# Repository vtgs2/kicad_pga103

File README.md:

# kicad_pga103

KiCAD Designs for PGA-103+ Preamplifier (LNA) intended for use in VHF / UHF Satellite Reception.  

This is a catchall repo for multiple designs and multiple variants.  
The variants will be based on physical size, enclosure dimensions, and specific features.  
This is a fluid repo that wil be changing as time allows to include updates for parts selection and user guide for how to configure for different bands.  

## Shut up and give me the board

Completed Designs:
- v2.0.0.0, rev-, Oct 2, 2023
- v2.1.X.0, rev-, Oct 2, 2023
- v2.2.X.0, rev-, Oct 2, 2023

#### Osh Park:
[v2.0.0.0, rev-](https://oshpark.com/shared_projects/KYiMNU72)  
[v2.1.X.0, rev-](https://oshpark.com/shared_projects/wypFvs1c)  
[v2.2.X.0, rev-](https://oshpark.com/shared_projects/yOYgdtt8)  

## Major Design Features

### Active Device
Primary active device is the popular [PGA-103+](https://www.minicircuits.com/WebStore/dashboard.html?model=PGA-103%2B).
Expect >20 dB Gain and <1.0 dB Noise Figure for both VHF and UHF bands.  

### Bias Options
Multiple biasing options via solder jumpers on the board.  
See board silkscreen for solder jumper settings for selecting the methods described below.

#### DC on Coax, +12V
The primary expected method for powering the board.  
This method routes DC power from the output RF connector to the internal voltage regulator for power conditioning, filtering, and biasing the amp.  
A bias-t will be required on the other end of the coax close to the radio.  
A custom Bias-T design may be added to this repo, but for now here are some COTS options:
- Minicircuits [ZDPLX-2150-S+](https://www.minicircuits.com/WebStore/dashboard.html?model=ZDPLX-2150-S%2B) where the Low Pass port is for DC. Be careful about current draw requirements if using long coax runs as this has a fairly low current limit of about 100mA.  Have succesfully used this on multiple compact systems in the past.
- Minicircuits [ZABT-2R15G+](https://www.minicircuits.com/WebStore/dashboard.html?model=ZABT-2R15G%2B). This Bias-T allows 3A of DC current and also includes ability to inject a 10 MHz reference signal (not needed for this specific preamp design, but might be useful for future projects for distributing REF oscillator signals to antenna mounted components such as downconverters).
- [Kuhne Electronic Bias-Ts](https://www.kuhne-electronic.com/funk/en/shop/industrial/prof-passive-compone/prof-bias-tees/).  Pricey, but work well. They offer N and SMA variants.

##### Lightning Arrestors
If using the DC on coax methods and if using lightning arrestors (you should be!), be sure to select arrestors that allow DC pass through.  I typically connect bias-ts directly to the lightning arrestors inside the enclosure on the 'equipment' side of the arrestor using barrel N or SMA connectors.

#### DC on Coax, Direct 5V
DC on coax can be routed to AVOID the onboard voltage regulator and directly bias the PGA-103+ device.  
This method may be suitable for SDRs that have built in Bias-Ts, such as the popular [RTL-SDR](https://www.rtl-sdr.com/buy-rtl-sdr-dvb-t-dongles/) that has a built in 4.5V bias-T.

#### External DC
This method does not interact with RF output connector and supplies power to the onboard voltage regulator.  
The supplied DC Voltage should be between 6V and 16V as measured at the board input pads (consider DC voltage drop if running long external power lines).  
The current mechanical designs for enclosure do not include penetrations for external power.  
If adding external power, feed through capacitors / EMI filters are recommended. Something like [this](https://www.digikey.com/en/products/detail/tusonix-a-subsidiary-of-cts-electronic-components/4400-034LF/2079728).

## Version Description
Versioning is inspired by MAJOR.MINOR.PATCH type versioning....but will also be breaking the rules for that on purpose.

Version Fields:  ENCLOSURE.FILTER.BAND.GAIN
##### ENCLOSURE:  
1.X.X.X  [1550Z101](https://www.digikey.com/en/products/detail/hammond-manufacturing/1550Z101/2268541)  
2.X.X.X  [AN-1301-A](https://www.digikey.com/en/products/detail/bud-industries/AN-1301-A/5804533)

Enclosure style essentially dictates the board outline.

##### FILTER Style:  
X.0.X.X  No Filter  
X.1.X.X  [RBP-XXX Filter](https://www.minicircuits.com/WebStore/dashboard.html?model=RBP-140%2B)  
X.2.X.X  [SBXP-XXX Filter](https://www.minicircuits.com/WebStore/dashboard.html?model=SXBP-140%2B)

##### BAND:   
X.X.0.X  Wideband  
X.X.1.X  VHF  
X.X.2.X  UHF  

Band selection depends on the filter selection and the choice of components for the bypass caps and bias-t inductors.

##### GAIN:   
X.X.X.0  Single Stage  
X.X.X.1  Dual Stage  

Curent completed designs only include the single gain stage preamplifiers.
Future designs may include a dual gain stage design for 'ultra-gain' type operation.

<!-- | Version | Enclosure  | Filter    | Description  | Design Complete |
| ------- | ---------- | --------- | ------------ | --------------- |
| 1.0.0   | 1550Z102   | False     |              | True |
| 1.1.X   | 1550Z102   | RBP-XXX   |              | True |
| 1.1.1   | 1550Z102   | RBP-140   | VHF Band     | True |
| 1.1.2    | 1550Z102   | RBP-440   | UHF Band     | True |
| 2.0.0.0 | AN-1301-A  | False     | Alt Encl: 1550Z104  | False |
| 2.1.X   | AN-1301-A  | RBP-XXX   |              | False |
| 2.1.1   | AN-1301-A  | RBP-140   | VHF Band     | False |
| 2.1.2   | AN-1301-A  | RBP-440   | UHF Band     | False |
| 2.2.X   | AN-1301-A  | SBXP-XXX  |              | False |
| 2.2.1   | AN-1301-A  | SBXP-140  | VHF Band     | False |
| 2.2.2   | AN-1301-A  | SBXP-440  | UHF Band     | False | -->

<!-- 

Multiple variants:
- Version 1: Unfiltered
- Version 2: Mini Circuits RBP-XXX Bandpass Filter
- Version 3: Mini Circuits SXBP-XXX Bandpass Filter
- Version 4: Dual Gain, RBP-XXX (Future)
- Version 5: Dual Gain, SXBP-XXX (Future) -->

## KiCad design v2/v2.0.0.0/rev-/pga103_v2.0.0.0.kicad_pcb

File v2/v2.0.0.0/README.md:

# PGA-103+ Preamplifier, Version 2.0.0.0

Enclosure: AN-1301-A  
Filter: None  
Band: Wideband  
Gain: Single Stage

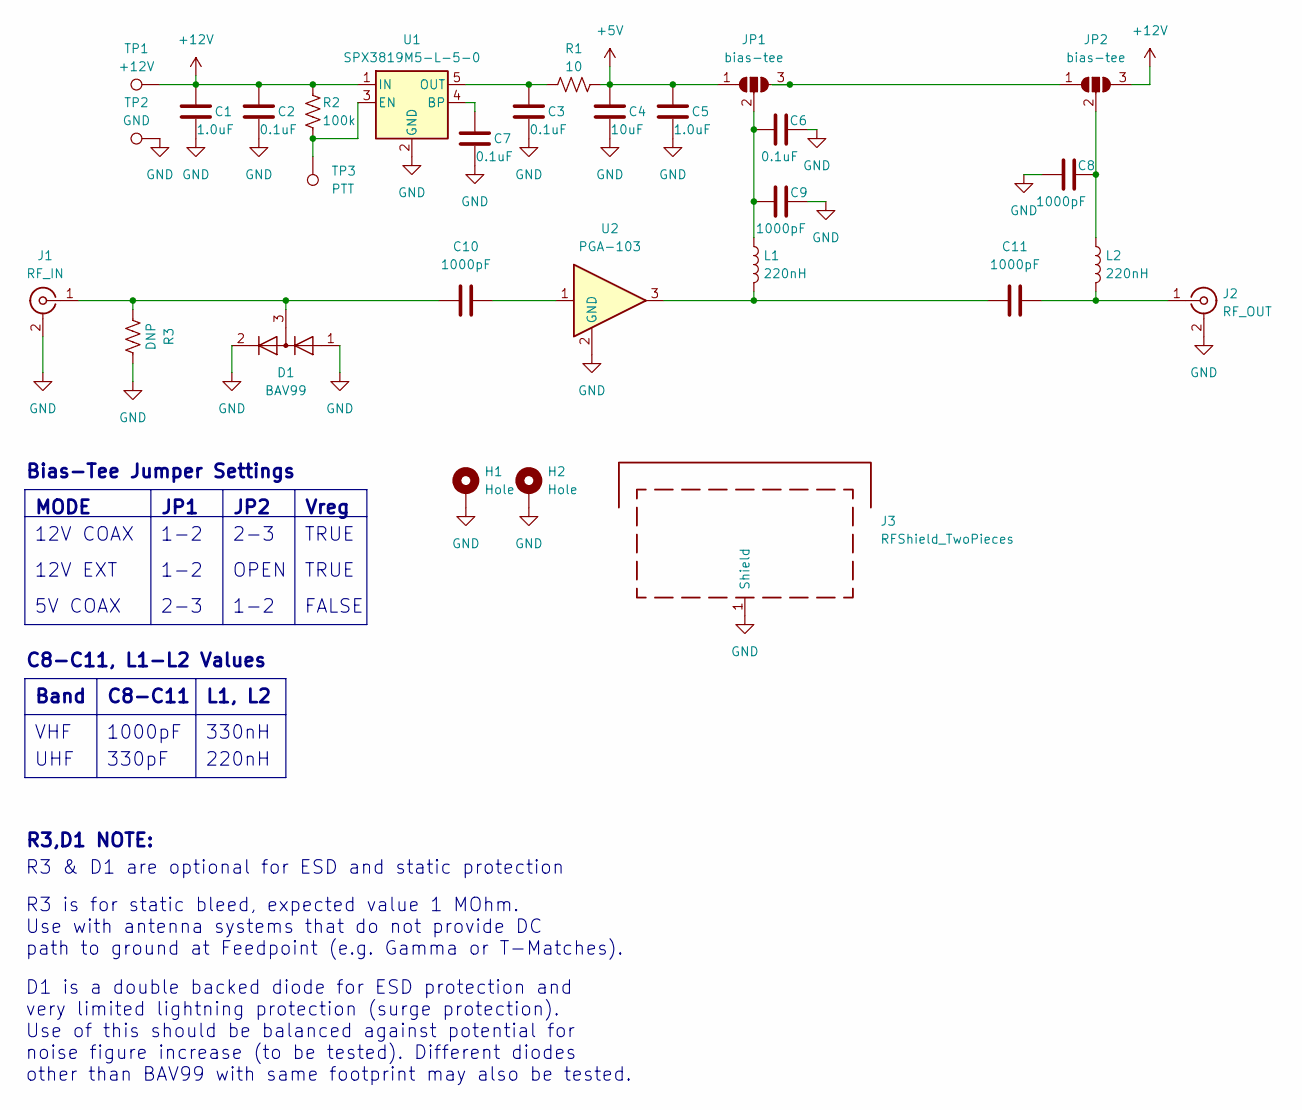
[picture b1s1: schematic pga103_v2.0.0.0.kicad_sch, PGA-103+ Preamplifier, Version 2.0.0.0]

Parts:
C1, C5: 1.0uF; 0805
C2, C3, C6, C7: 0.1uF; 0805
C4: 10uF; 0805
C8, C9, C10, C11: 1000pF; 0805
D1: BAV99; SOT-23
H1, H2: Hole; TestPoint_Plated_Hole_D4.0mm
J1: RF_IN; SMA_Samtec_SMA-J-P-X-ST-EM1_EdgeMount
J2: RF_OUT; SMA_Samtec_SMA-J-P-X-ST-EM1_EdgeMount
J3: RFShield_TwoPieces; Wuerth_36103205_20x20mm
JP1, JP2: bias-tee; SolderJumper-3_P1.3mm_Open_RoundedPad1.0x1.5mm_NumberLabels
L1, L2: 220nH; 0805
R1: 10; 0805
R2: 100k; 0805
R3: DNP; 0805
TP1: +12V; TestPoint_Pad_2.0x2.0mm
TP2: GND; TestPoint_Pad_2.0x2.0mm
TP3: PTT; TestPoint_Pad_2.0x2.0mm
U1: SPX3819M5-L-5-0; SOT-23-5
U2: PGA-103; SOT-89-3

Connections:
+5V: C4.2, C5.2, JP1.1 (A), R1.2
+12V: C1.2, C2.2, JP2.3 (B), R2.1, TP1.1, U1.1 (IN)
GND: C1.1, C2.1, C3.1, C4.1, C5.1, C6.1, C7.1, C8.2, C9.1, D1.1 (K), D1.2 (A), H1.1, H2.1, J1.2 (Ext), J2.2 (Ext), J3.1 (Shield), R3.2, TP2.1, U1.2 (GND), U2.2 (GND)
unnamed: C10.2, U2.1
unnamed: C11.1, L1.2, U2.3
unnamed: C10.1, D1.3 (K), J1.1 (In), R3.1
unnamed: C11.2, J2.1 (In), L2.2
unnamed: JP1.3 (B), JP2.1 (A)
unnamed: C6.2, C9.2, JP1.2 (C), L1.1
unnamed: C8.1, JP2.2 (C), L2.1
unnamed: C7.2, U1.4 (BP)
unnamed: R2.2, TP3.1, U1.3 (EN)
unnamed: C3.2, R1.1, U1.5 (OUT)

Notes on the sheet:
UHF
2-3
TRUE
R3 is for static bleed, expected value 1 MOhm. Use with antenna systems that do not provide DC path to ground at Feedpoint (e.g. Gamma or T-Matches).
330nH
D1 is a double backed diode for ESD protection and very limited lightning protection (surge protection). Use of this should be balanced against potential for noise figure increase (to be tested). Different diodes other than BAV99 with same footprint may also be tested.
330pF
C8-C11
VHF
OPEN
R3,D1 NOTE:
Bias-Tee Jumper Settings
JP1
R3 & D1 are optional for ESD and static protection
JP2
C8-C11, L1-L2 Values
12V COAX
1-2
Vreg
220nH
1000pF
MODE
5V COAX
Band
L1, L2
12V EXT
FALSE

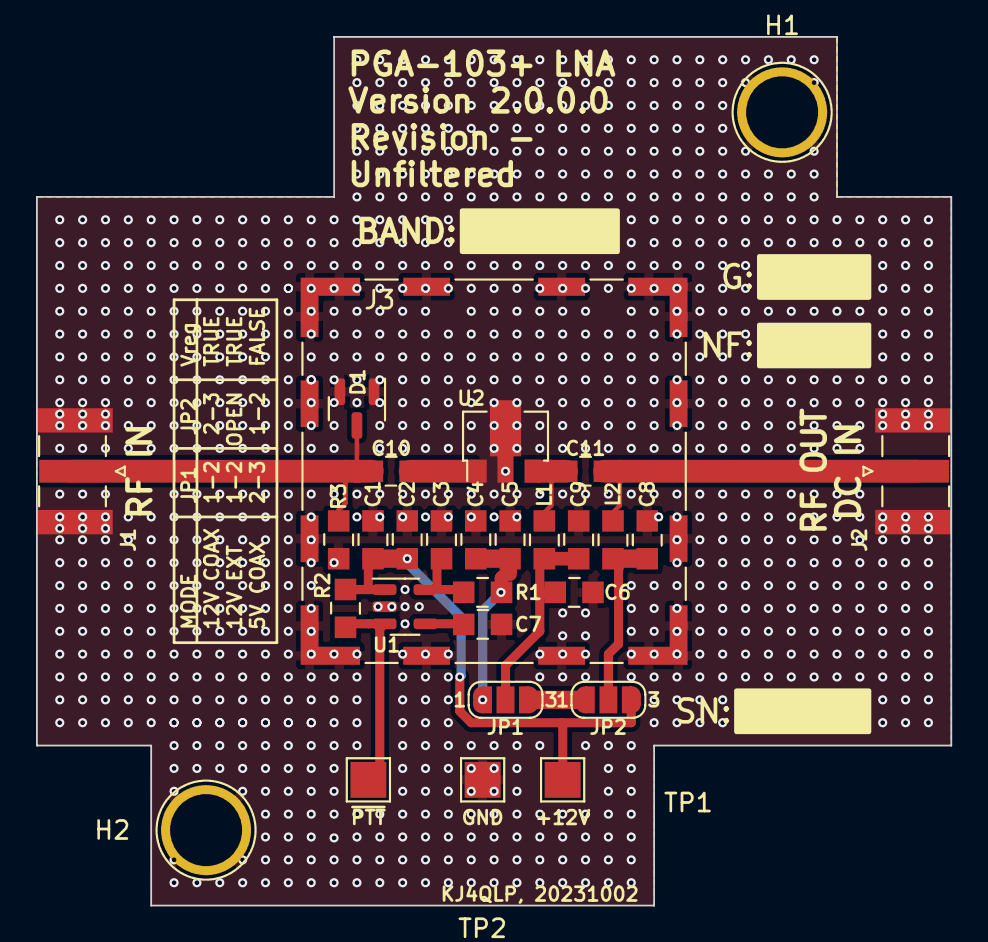
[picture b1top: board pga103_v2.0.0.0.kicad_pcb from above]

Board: 2 copper layers, 50.8 x 48.3 mm, 29 parts (0 on the bottom side), 13 nets.

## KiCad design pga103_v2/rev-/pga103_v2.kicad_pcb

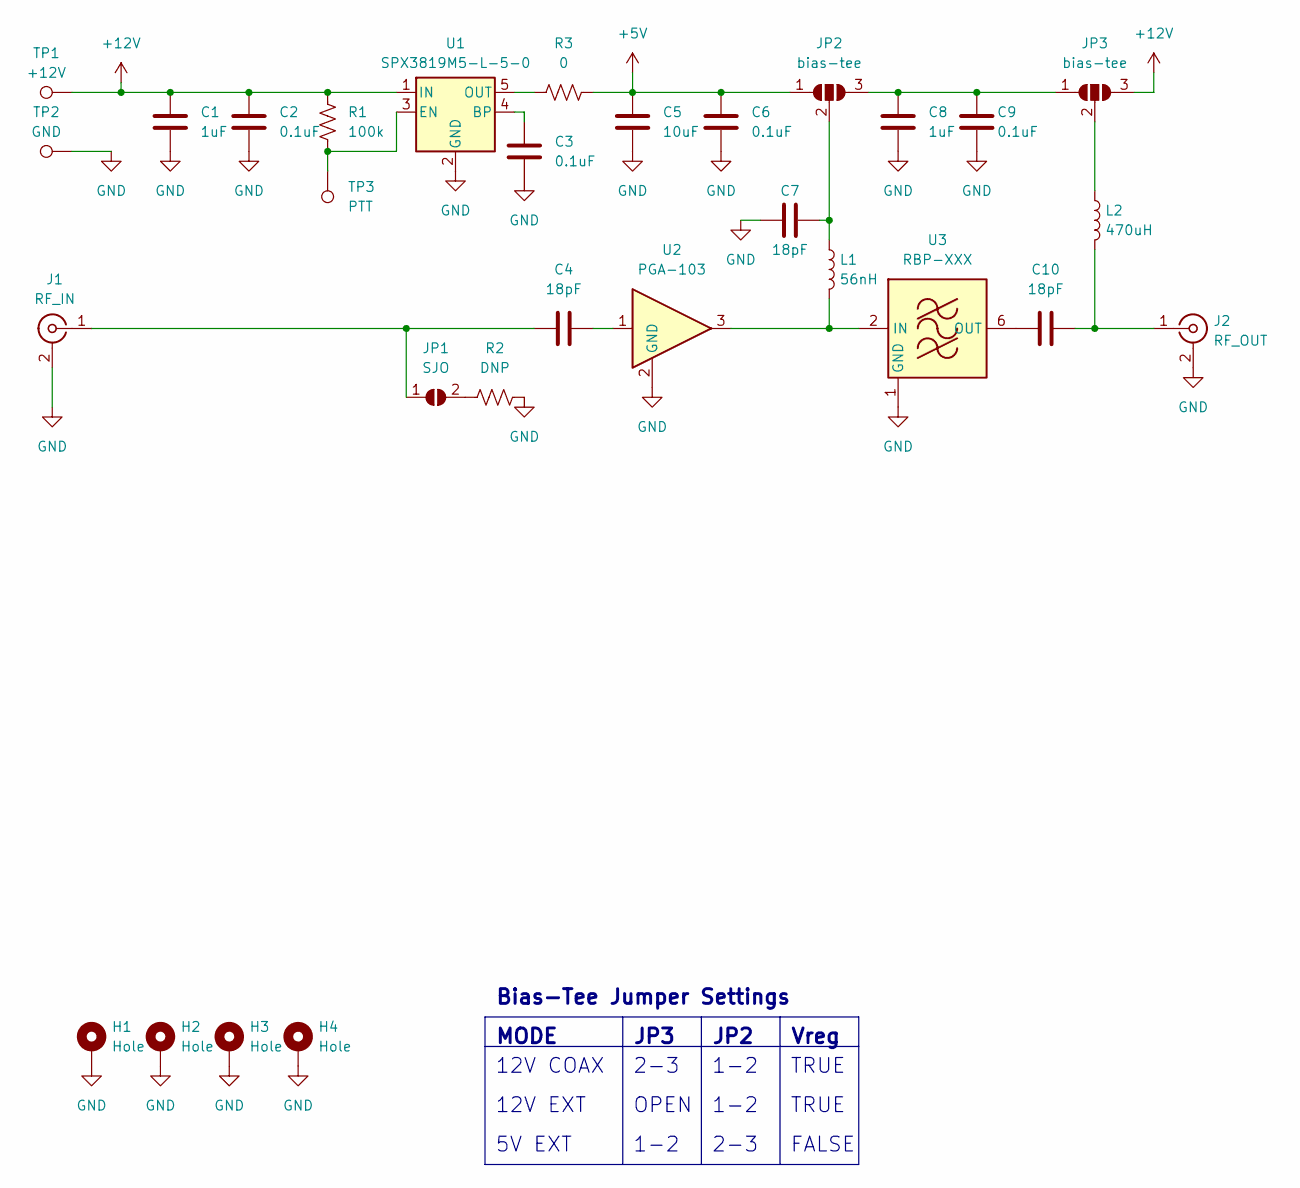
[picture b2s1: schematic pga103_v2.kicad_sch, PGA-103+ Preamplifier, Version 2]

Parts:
C1, C8: 1uF; 0805
C2, C3, C6, C9: 0.1uF; 0805
C4, C7, C10: 18pF; 0805
C5: 10uF; 0805
H1, H2, H3, H4: Hole; MountingHole_2.5mm_Pad_Via
J1: RF_IN; SMA_Samtec_SMA-J-P-X-ST-EM1_EdgeMount
J2: RF_OUT; SMA_Samtec_SMA-J-P-X-ST-EM1_EdgeMount
JP1: SJO; SolderJumper-2_P1.3mm_Open_RoundedPad1.0x1.5mm
JP2, JP3: bias-tee; SolderJumper-3_P1.3mm_Open_RoundedPad1.0x1.5mm_NumberLabels
L1: 56nH; 0805
L2: 470uH; 0805
R1: 100k; 0805
R2: DNP; 0805
R3: 0; 0805
TP1: +12V; TestPoint_Pad_2.0x2.0mm
TP2: GND; TestPoint_Pad_2.0x2.0mm
TP3: PTT; TestPoint_Pad_2.0x2.0mm
U1: SPX3819M5-L-5-0; SOT-23-5
U2: PGA-103; SOT-89-3
U3: RBP-XXX; Mini-Circuits_GP731_LandPatternPL-176

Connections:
+5V: C5.2, C6.2, JP2.1 (A), R3.2
+12V: C1.2, C2.2, JP3.3 (B), R1.1, TP1.1, U1.1 (IN)
GND: C1.1, C2.1, C3.1, C5.1, C6.1, C7.1, C8.1, C9.1, H1.1, H2.1, H3.1, H4.1, J1.2 (Ext), J2.2 (Ext), R2.2, TP2.1, U1.2 (GND), U2.2 (GND), U3.1 (GND), U3.3 (GND), U3.4 (GND), U3.5 (GND), U3.7 (GND), U3.8 (GND)
unnamed: C4.2, U2.1
unnamed: C4.1, J1.1 (In), JP1.1 (A)
unnamed: C10.2, J2.1 (In), L2.2
unnamed: JP1.2 (B), R2.1
unnamed: C8.2, C9.2, JP2.3 (B), JP3.1 (A)
unnamed: C7.2, JP2.2 (C), L1.1
unnamed: JP3.2 (C), L2.1
unnamed: C3.2, U1.4 (BP)
unnamed: R1.2, TP3.1, U1.3 (EN)
unnamed: R3.1, U1.5 (OUT)
unnamed: L1.2, U2.3, U3.2 (IN)
unnamed: C10.1, U3.6 (OUT)

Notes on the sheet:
2-3
TRUE
OPEN
Bias-Tee Jumper Settings
JP2
JP3
12V COAX
1-2
Vreg
MODE
5V EXT
12V EXT
FALSE

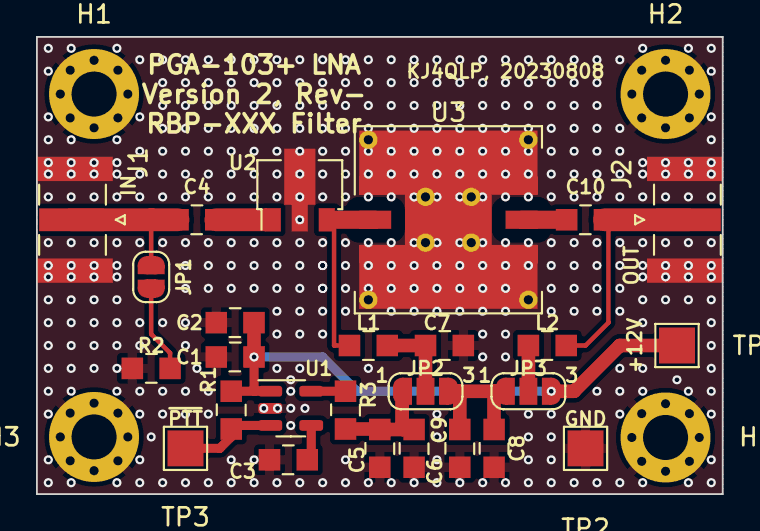
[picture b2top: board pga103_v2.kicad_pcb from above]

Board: 2 copper layers, 38.1 x 25.4 mm, 30 parts (0 on the bottom side), 15 nets.

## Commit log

2023-08-08 multiple variants of pga-103 preamp design
2023-08-22 added pngs of board
2023-08-22 fixed silk screen for dimensions in V1
2023-09-21 updating board edge and adding shielding
2023-09-25 finalized V1 schematic and board
2023-09-25 forgot to save last commit.....
2023-09-25 initial commit of BOM, incomplete.
2023-09-26 aded gitignore, about to rearrange for MAJOR.MINOR.PATCH versioning
2023-09-26 rearranged existing projects for new versioning scheme
2023-10-02 adding updated versions.....close to ready for fab
2023-10-02 added readme
2023-10-02 added oshpark generated images of pcb.
2023-10-02 added osh park images for v2 boards. PCBs at this commit submitted to Osh PArk
2023-10-11 edited BOM, rearranged folders structure, added mechanical diagram for V2, updated readme.
2023-10-30 added pdf of schematic, board population checklist, fixed typo in V2.0.0.0 title

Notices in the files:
pga103_v2/rev-/pga103_v2.kicad_pcb:
creativecommons.org/licenses/by/4.0
License: CC BY 4.0
